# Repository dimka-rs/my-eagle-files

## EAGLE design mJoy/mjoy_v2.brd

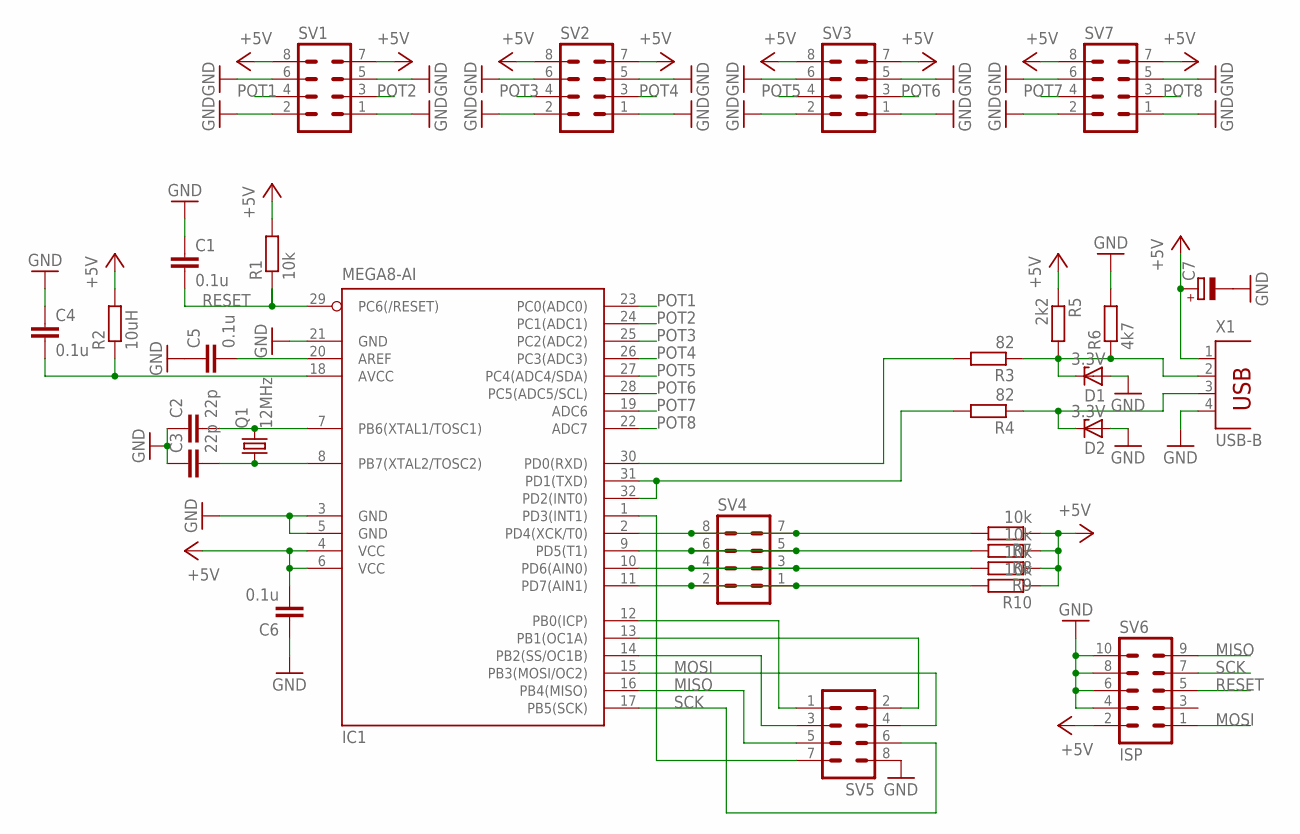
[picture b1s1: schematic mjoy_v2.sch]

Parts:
C1, C4, C5, C6: 0.1u; C0805
C2, C3: 22p; C0805
C7: CPOL-EUSMCD; SMC_D
D1, D2: 3.3V; SOD80C
IC1: MEGA8-AI; TQFP32-08
Q1: 12MHz; HC49UP
R1, R7, R8, R9, R10: 10k; R0805
R2: 10uH; R1210
R3, R4: 82; R0805
R5: 2k2; R0805
R6: 4k7; R0805
SV1, SV2, SV3, SV4, SV5, SV7: MA04-2
SV6: ISP; MA05-2
X1: USB-B; PN61729

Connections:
+5V: C6.2, C7.+, IC1.4 (VCC), IC1.6 (VCC), R1.2, R2.2, R5.1, R7.1, R8.1, R9.1, R10.1, SV1.7, SV1.8, SV2.7, SV2.8, SV3.7, SV3.8, SV6.2, SV7.7, SV7.8, X1.1
AREF: C5.2, IC1.20 (AREF)
GND: C1.1, C2.1, C3.1, C4.1, C5.1, C6.1, C7.-, D1.A, D2.A, IC1.3 (GND), IC1.5 (GND), IC1.21 (GND), R6.2, SV1.1, SV1.2, SV1.5, SV1.6, SV2.1, SV2.2, SV2.5, SV2.6, SV3.1, SV3.2, SV3.5, SV3.6, SV5.8, SV6.4, SV6.6, SV6.8, SV6.10, SV7.1, SV7.2, SV7.5, SV7.6, X1.4
MISO: IC1.16 (PB4(MISO)), SV5.5, SV6.9
MOSI: IC1.15 (PB3(MOSI/OC2)), SV5.4, SV6.1
unnamed: IC1.12 (PB0(ICP)), SV5.1
unnamed: C4.2, IC1.18 (AVCC), R2.1
unnamed: IC1.13 (PB1(OC1A)), SV5.2
unnamed: C3.2, IC1.8 (PB7(XTAL2/TOSC2)), Q1.1
unnamed: C2.2, IC1.7 (PB6(XTAL1/TOSC1)), Q1.2
unnamed: IC1.14 (PB2(SS/OC1B)), SV5.3
unnamed: IC1.30 (PD0(RXD)), R3.2
unnamed: IC1.31 (PD1(TXD)), IC1.32 (PD2(INT0)), R4.2
unnamed: D1.C, R3.1, R5.2, R6.1, X1.2
unnamed: D2.C, R4.1, X1.3
unnamed: IC1.2 (PD4(XCK/T0)), R7.2, SV4.7, SV4.8
unnamed: IC1.9 (PD5(T1)), R8.2, SV4.5, SV4.6
unnamed: IC1.10 (PD6(AIN0)), R9.2, SV4.3, SV4.4
unnamed: IC1.11 (PD7(AIN1)), R10.2, SV4.1, SV4.2
unnamed: IC1.1 (PD3(INT1)), SV5.7
POT1: IC1.23 (PC0(ADC0)), SV1.4
POT2: IC1.24 (PC1(ADC1)), SV1.3
POT3: IC1.25 (PC2(ADC2)), SV2.4
POT4: IC1.26 (PC3(ADC3)), SV2.3
POT5: IC1.27 (PC4(ADC4/SDA)), SV3.4
POT6: IC1.28 (PC5(ADC5/SCL)), SV3.3
POT7: IC1.19 (ADC6), SV7.4
POT8: IC1.22 (ADC7), SV7.3
RESET: C1.2, IC1.29 (PC6(/RESET)), R1.1, SV6.5
SCK: IC1.17 (PB5(SCK)), SV5.6, SV6.7

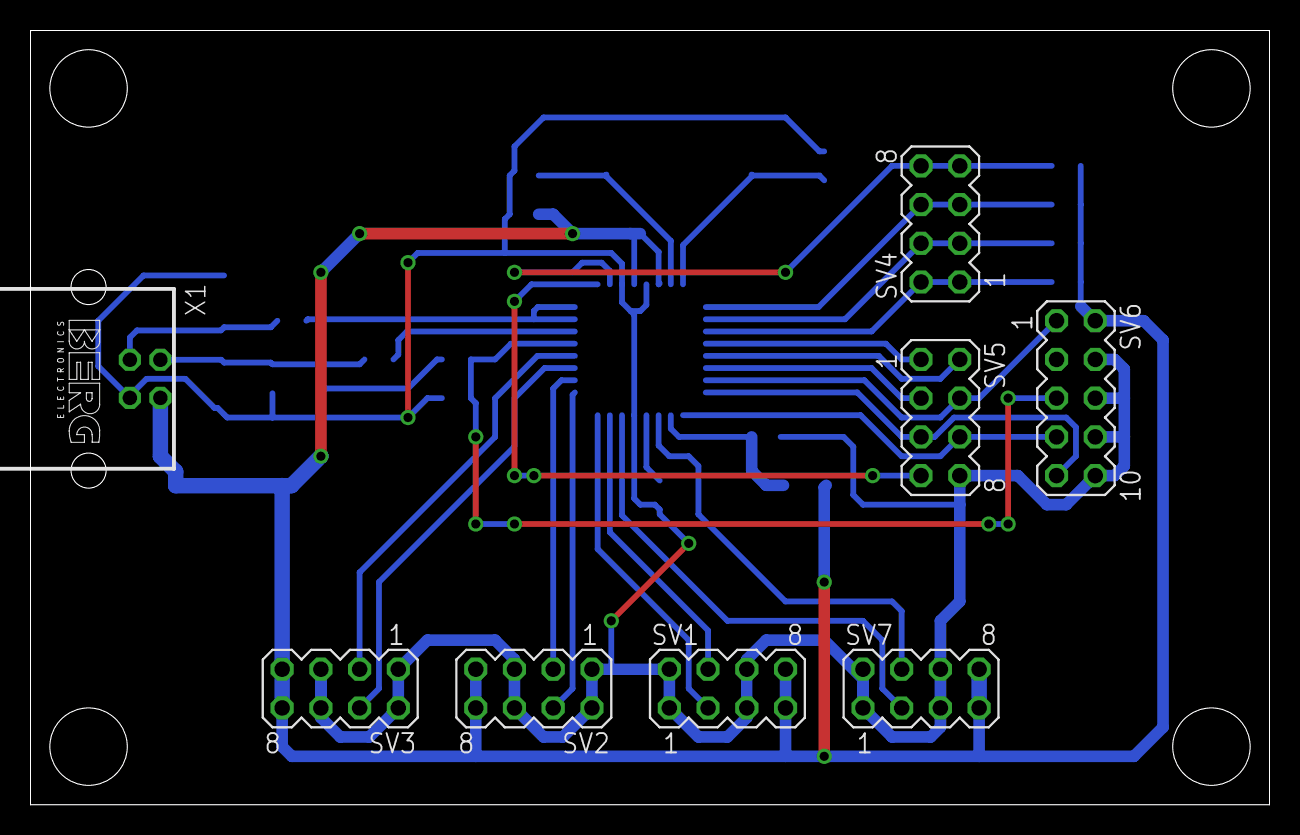
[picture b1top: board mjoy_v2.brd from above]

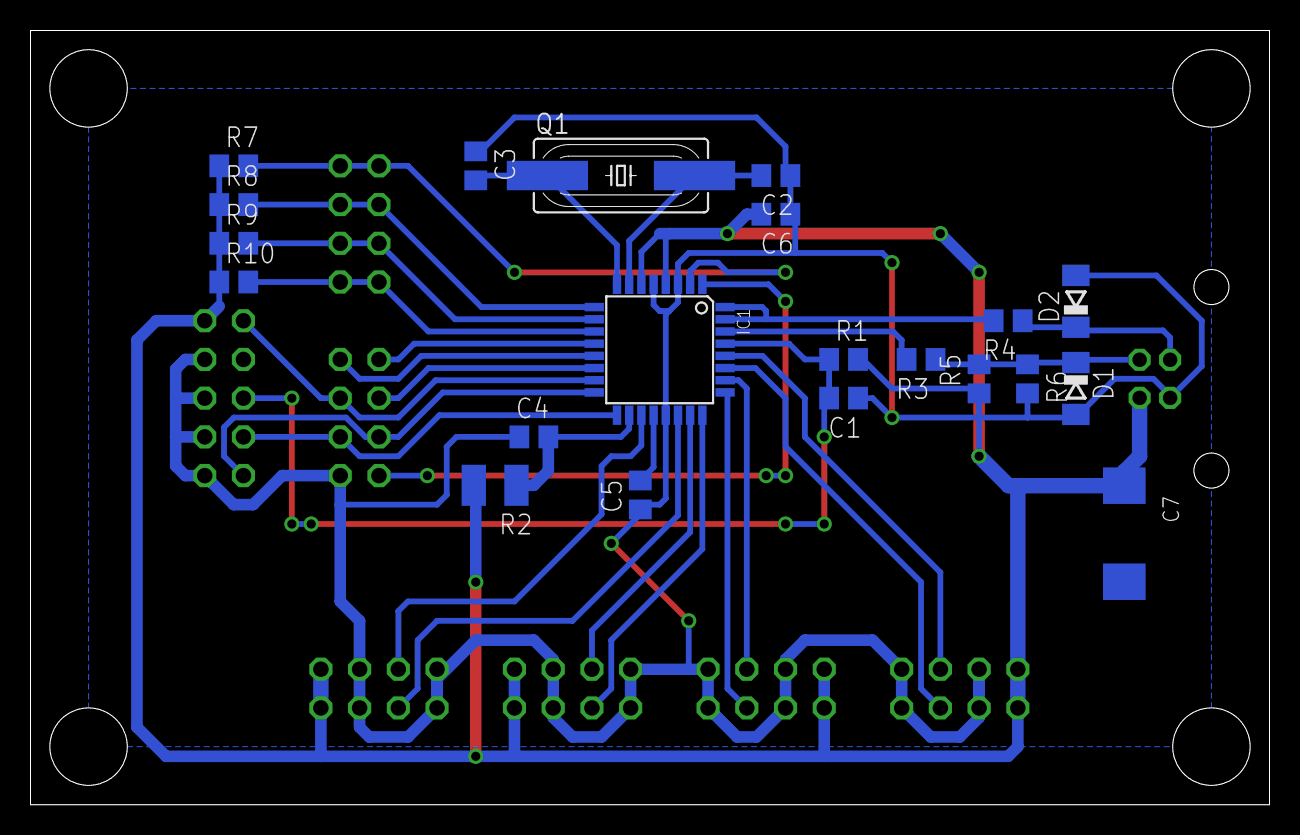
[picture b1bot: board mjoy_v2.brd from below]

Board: 2 copper layers, 81.3 x 50.8 mm, 29 parts (21 on the bottom side), 30 nets.

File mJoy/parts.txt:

Partlist

Exported from mjoy.sch at 07.09.09 1:41

EAGLE Version 5.6.0 Copyright (c) 1988-2009 CadSoft

Part     Value          Device            Package     Library  Sheet

C1       0.1u           C-EUC0805         C0805       rcl      1
C2       22p            C-EUC0805         C0805       rcl      1
C3       22p            C-EUC0805         C0805       rcl      1
C4       0.1u           C-EUC0805         C0805       rcl      1
C5       0.1u           C-EUC0805         C0805       rcl      1
C6       0.1u           C-EUC0805         C0805       rcl      1
C7       100u           CPOL-EUE          PANASONIC_E rcl      1
D1       3.3V           ZENER-DIODESOD80C SOD80C      diode    1
D2       3.3V           ZENER-DIODESOD80C SOD80C      diode    1
IC1      MEGA8-AI       MEGA8-AI          TQFP32-08   atmel    1
Q1       12MHz          CRYSTALHC49UP     HC49UP      crystal  1
R1       10k            R-EU_R0805        R0805       rcl      1
R2       10uH           R-EU_R1210        R1210       rcl      1
R3       82             R-EU_R0805        R0805       rcl      1
R4       82             R-EU_R0805        R0805       rcl      1
R5       2k2            R-EU_R0805        R0805       rcl      1
R6       4k7            R-EU_R0805        R0805       rcl      1
R7       10k            R-EU_R0805        R0805       rcl      1
R8       10k            R-EU_R0805        R0805       rcl      1
R9       10k            R-EU_R0805        R0805       rcl      1
R10      10k            R-EU_R0805        R0805       rcl      1
SV1      R_SIG          MA08-1            MA08-1      con-lstb 1
SV2      R_GND          MA08-1            MA08-1      con-lstb 1
SV3      R_VCC          MA08-1            MA08-1      con-lstb 1
SV4      BUT_X          MA04-1            MA04-1      con-lstb 1
SV5      BUT_Y          MA07-1            MA07-1      con-lstb 1
SV6      ISP            MA05-2            MA05-2      con-lstb 1
SV8      R_AREF         MA03-1            MA03-1      con-lstb 1
SV9      R_AGND         MA03-1            MA03-1      con-lstb 1
X1       USB-B          PN61729           PN61729     con-berg 1

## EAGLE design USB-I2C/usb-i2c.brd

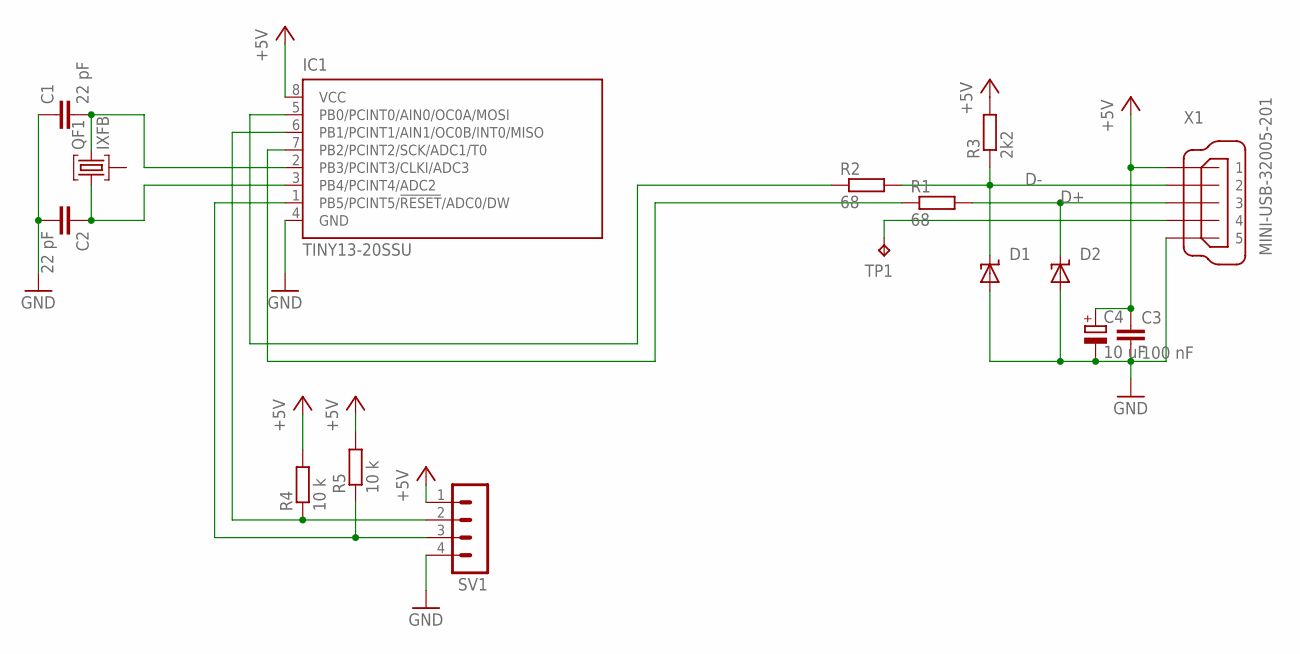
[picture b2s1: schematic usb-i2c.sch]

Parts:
C1, C2: 22 pF; C0603K
C3: 100 nF; C0603K
C4: 10 uF; E2,5-6E
D1, D2: SUPPRESSOR-SMBJ; SMBJ
IC1: TINY13-20SSU; 8S1
QF1: IXFB; UM1
R1, R2: 68; R0603
R3: 2k2; R0603
R4, R5: 10 k; R0603
SV1: MA04-1
TP1: TPB2,54; B2,54
X1: MINI-USB-32005-201; 32005-201

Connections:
+5V: C3.1, C4.+, IC1.8 (VCC), R3.2, R4.2, R5.2, SV1.1, X1.1
D+: D2.C, R1.2, X1.3
D-: D1.C, R2.2, R3.1, X1.2
GND: C1.1, C2.2, C3.2, C4.-, D1.A, D2.A, IC1.4 (GND), SV1.4, X1.5
unnamed: IC1.5 (PB0/PCINT0/AIN0/OC0A/MOSI), R2.1
unnamed: C2.1, IC1.3 (PB4/PCINT4/ADC2), QF1.1
unnamed: C1.2, IC1.2 (PB3/PCINT3/CLKI/ADC3), QF1.3
unnamed: IC1.7 (PB2/PCINT2/SCK/ADC1/T0), R1.1
unnamed: IC1.6 (PB1/PCINT1/AIN1/OC0B/INT0/MISO), R4.1, SV1.2
unnamed: IC1.1 (PB5/PCINT5/!RESET!/ADC0/DW), R5.1, SV1.3
unnamed: TP1.TP, X1.4

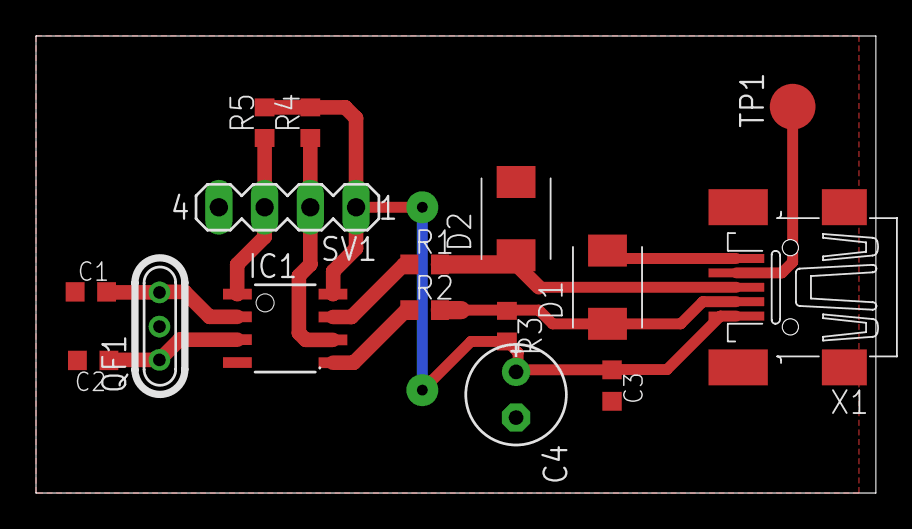
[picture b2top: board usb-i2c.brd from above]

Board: 2 copper layers, 46.7 x 25.4 mm, 16 parts (0 on the bottom side), 11 nets.

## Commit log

2010-11-11 All my files
2011-01-02 Radiotronix: New PCB
2011-01-02 git: added .gitignore file
2011-01-02 git: *~ files removed
2014-02-06 Added USB-I2C project
2014-02-06 USB-I2C: added description
2014-08-17 mJoy: updated to Eagle v7. C7 replaced with TANT-D
2014-08-17 STK200: update eagle to v7.
2014-08-17 STK200: updated Eagle to v7.
2015-02-18 jura initial
    added jura pcb reverse
2015-02-18 Revert "STK200: updated Eagle to v7."
    This reverts commit d5812fbd512d384a26ae25d27ba49cc661294cf7.
    Conflicts:
    STK200/eagle.epf
2015-02-18 Revert "Revert "STK200: updated Eagle to v7.""
    This reverts commit 92c92f12cc73deb109dc3424bd3930b07904c4d7.
2015-03-01 more reversing
2015-12-05 added ikea night light sch
